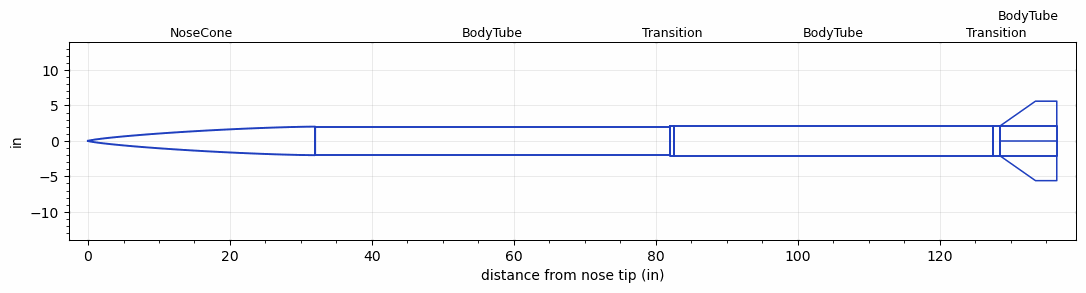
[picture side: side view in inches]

<RASAeroDocument>
 <FileVersion>2</FileVersion>
 <RocketDesign>
  <NoseCone>
   <Length>32</Length>
   <Diameter>4.02</Diameter>
   <Shape>Von Karman Ogive</Shape>
   <Location>0</Location>
  </NoseCone>
  <BodyTube>
   <Length>50</Length>
   <Diameter>4.02</Diameter>
   <Location>32</Location>
   <Protuberance>
    <StreamlinedNoBaseDrag>0.3693967</StreamlinedNoBaseDrag>
    <StreamlinedWithBaseDrag>0</StreamlinedWithBaseDrag>
    <InclinedPlate1Angle>0</InclinedPlate1Angle>
    <InclinedPlate1FrontalArea>0</InclinedPlate1FrontalArea>
    <InclinedPlate2Angle>0</InclinedPlate2Angle>
    <InclinedPlate2FrontalArea>0</InclinedPlate2FrontalArea>
   </Protuberance>
  </BodyTube>
  <Transition>
   <Length>0.5</Length>
   <Diameter>4.17</Diameter>
   <Location>82</Location>
   <RearDiameter>4.17</RearDiameter>
  </Transition>
  <BodyTube>
   <Length>45</Length>
   <Diameter>4.17</Diameter>
   <Location>82.5</Location>
  </BodyTube>
  <Transition>
   <Length>1</Length>
   <Diameter>4.2</Diameter>
   <Location>127.5</Location>
   <RearDiameter>4.2</RearDiameter>
  </Transition>
  <BodyTube>
   <Length>8</Length>
   <Diameter>4.2</Diameter>
   <Location>128.5</Location>
   <Fin>
    <Count>4</Count>
    <Chord>8</Chord>
    <Span>3.5</Span>
    <SweepDistance>5</SweepDistance>
    <TipChord>3</TipChord>
    <Thickness>0.25</Thickness>
    <Location>8</Location>
    <AirfoilSection>Hexagonal Blunt Base</AirfoilSection>
    <FX1>0.7469705</FX1>
   </Fin>
  </BodyTube>
  <Surface>Rough Camouflage Paint</Surface>
  <ModifiedBarrowman>False</ModifiedBarrowman>
  <Turbulence>False</Turbulence>
  <UseBooster1>False</UseBooster1>
  <UseBooster2>False</UseBooster2>
  <Comments>Iris half-inch sustainer static aero: finned</Comments>
 </RocketDesign>
 <LaunchSite>
  <Altitude>0</Altitude>
  <Pressure>29.9214</Pressure>
  <RodAngle>0</RodAngle>
  <RodLength>3.2808</RodLength>
  <Temperature>59</Temperature>
  <WindSpeed>0.25</WindSpeed>
 </LaunchSite>
 <Recovery>
  <Altitude1>0</Altitude1>
  <Altitude2>0</Altitude2>
  <DeviceType1>None</DeviceType1>
  <DeviceType2>None</DeviceType2>
  <Event1>False</Event1>
  <Event2>False</Event2>
  <Size1>0</Size1>
  <Size2>0</Size2>
  <EventType1>None</EventType1>
  <EventType2>None</EventType2>
  <CD1>0</CD1>
  <CD2>0</CD2>
 </Recovery>
 <SimulationList>
  <Simulation>
   <SustainerEngine>N3367  (CoefficientProbe)</SustainerEngine>
   <SustainerLaunchWt>24.25085</SustainerLaunchWt>
   <SustainerCG>75</SustainerCG>
   <SustainerIgnitionDelay>0</SustainerIgnitionDelay>
   <IncludeBooster1>False</IncludeBooster1>
   <IncludeBooster2>False</IncludeBooster2>
  </Simulation>
 </SimulationList>
</RASAeroDocument>
